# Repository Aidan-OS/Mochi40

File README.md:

# Mochi40
A 40% keyboard with an OLED and rotary encoder.

Files found on this GitHub should be fully functional. For more information come reach out [on my discord](https://discord.gg/kkPBkA3x4q)

# Ordering Guide
TODO

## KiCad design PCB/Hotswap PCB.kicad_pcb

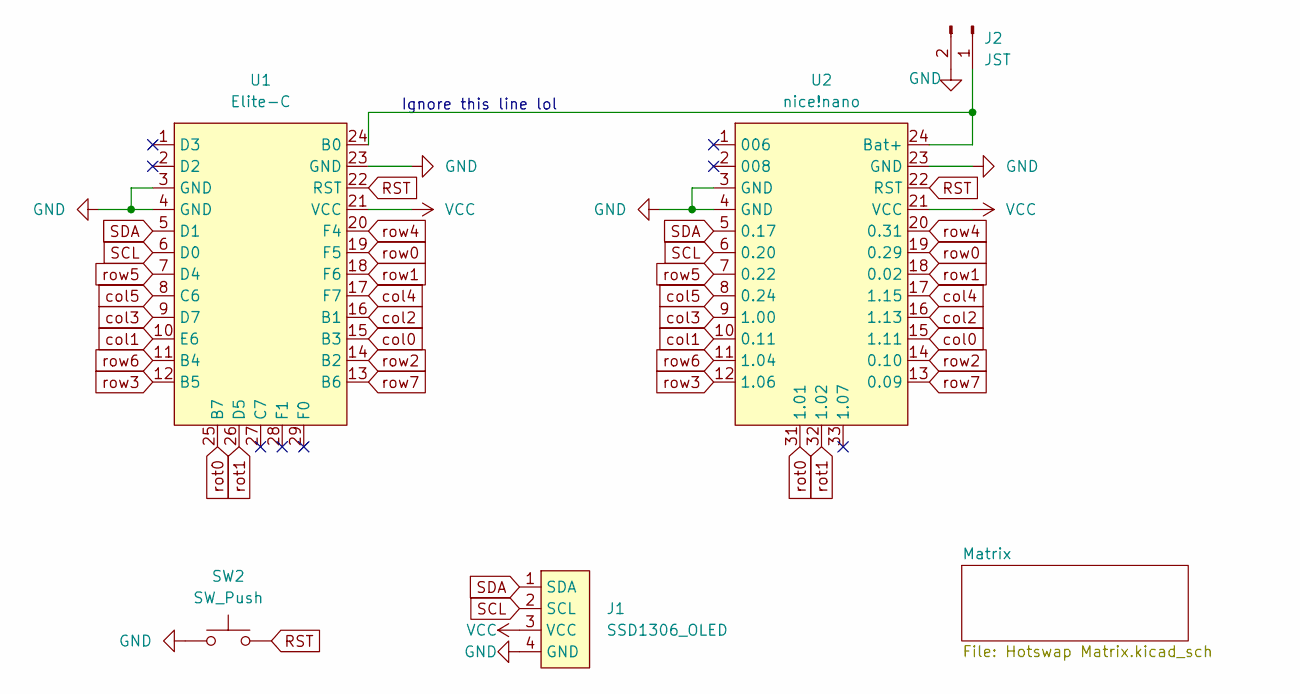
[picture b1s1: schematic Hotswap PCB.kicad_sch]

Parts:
J1: SSD1306_OLED; OLED_v2
J2: JST; JST_PH_S2B-PH-K_1x02_P2.00mm_Horizontal
SW2: SW_Push; SW_Tactile_SPST_Angled_MJTP1117
U1: Elite-C
U2: nice!nano; nice_nano

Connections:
GND: J1.4 (GND), J2.2, SW2.1, U1.3 (GND), U1.4 (GND), U1.23 (GND), U2.3 (GND), U2.4 (GND), U2.23 (GND); also elsewhere on the board
unnamed: J2.1, U1.24 (B0), U2.24 (Bat+)
RST: SW2.2, U1.22 (RST), U2.22 (RST)
SCL: J1.2 (SCL), U1.6 (D0), U2.6 (0.20)
SDA: J1.1 (SDA), U1.5 (D1), U2.5 (0.17)
VCC: J1.3 (VCC), U1.21 (VCC), U2.21 (VCC)
col0: U1.15 (B3), U2.15 (1.11); also elsewhere on the board
col1: U1.10 (E6), U2.10 (0.11); also elsewhere on the board
col2: U1.16 (B1), U2.16 (1.13); also elsewhere on the board
col3: U1.9 (D7), U2.9 (1.00); also elsewhere on the board
col4: U1.17 (F7), U2.17 (1.15); also elsewhere on the board
col5: U1.8 (C6), U2.8 (0.24); also elsewhere on the board
rot0: U1.25 (B7), U2.31 (1.01); also elsewhere on the board
rot1: U1.26 (D5), U2.32 (1.02); also elsewhere on the board
row0: U1.19 (F5), U2.19 (0.29); also elsewhere on the board
row1: U1.18 (F6), U2.18 (0.02); also elsewhere on the board
row2: U1.14 (B2), U2.14 (0.10); also elsewhere on the board
row3: U1.12 (B5), U2.12 (1.06); also elsewhere on the board
row4: U1.20 (F4), U2.20 (0.31); also elsewhere on the board
row5: U1.7 (D4), U2.7 (0.22); also elsewhere on the board
row6: U1.11 (B4), U2.11 (1.04); also elsewhere on the board
row7: U1.13 (B6), U2.13 (0.09); also elsewhere on the board

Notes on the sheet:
Ignore this line lol

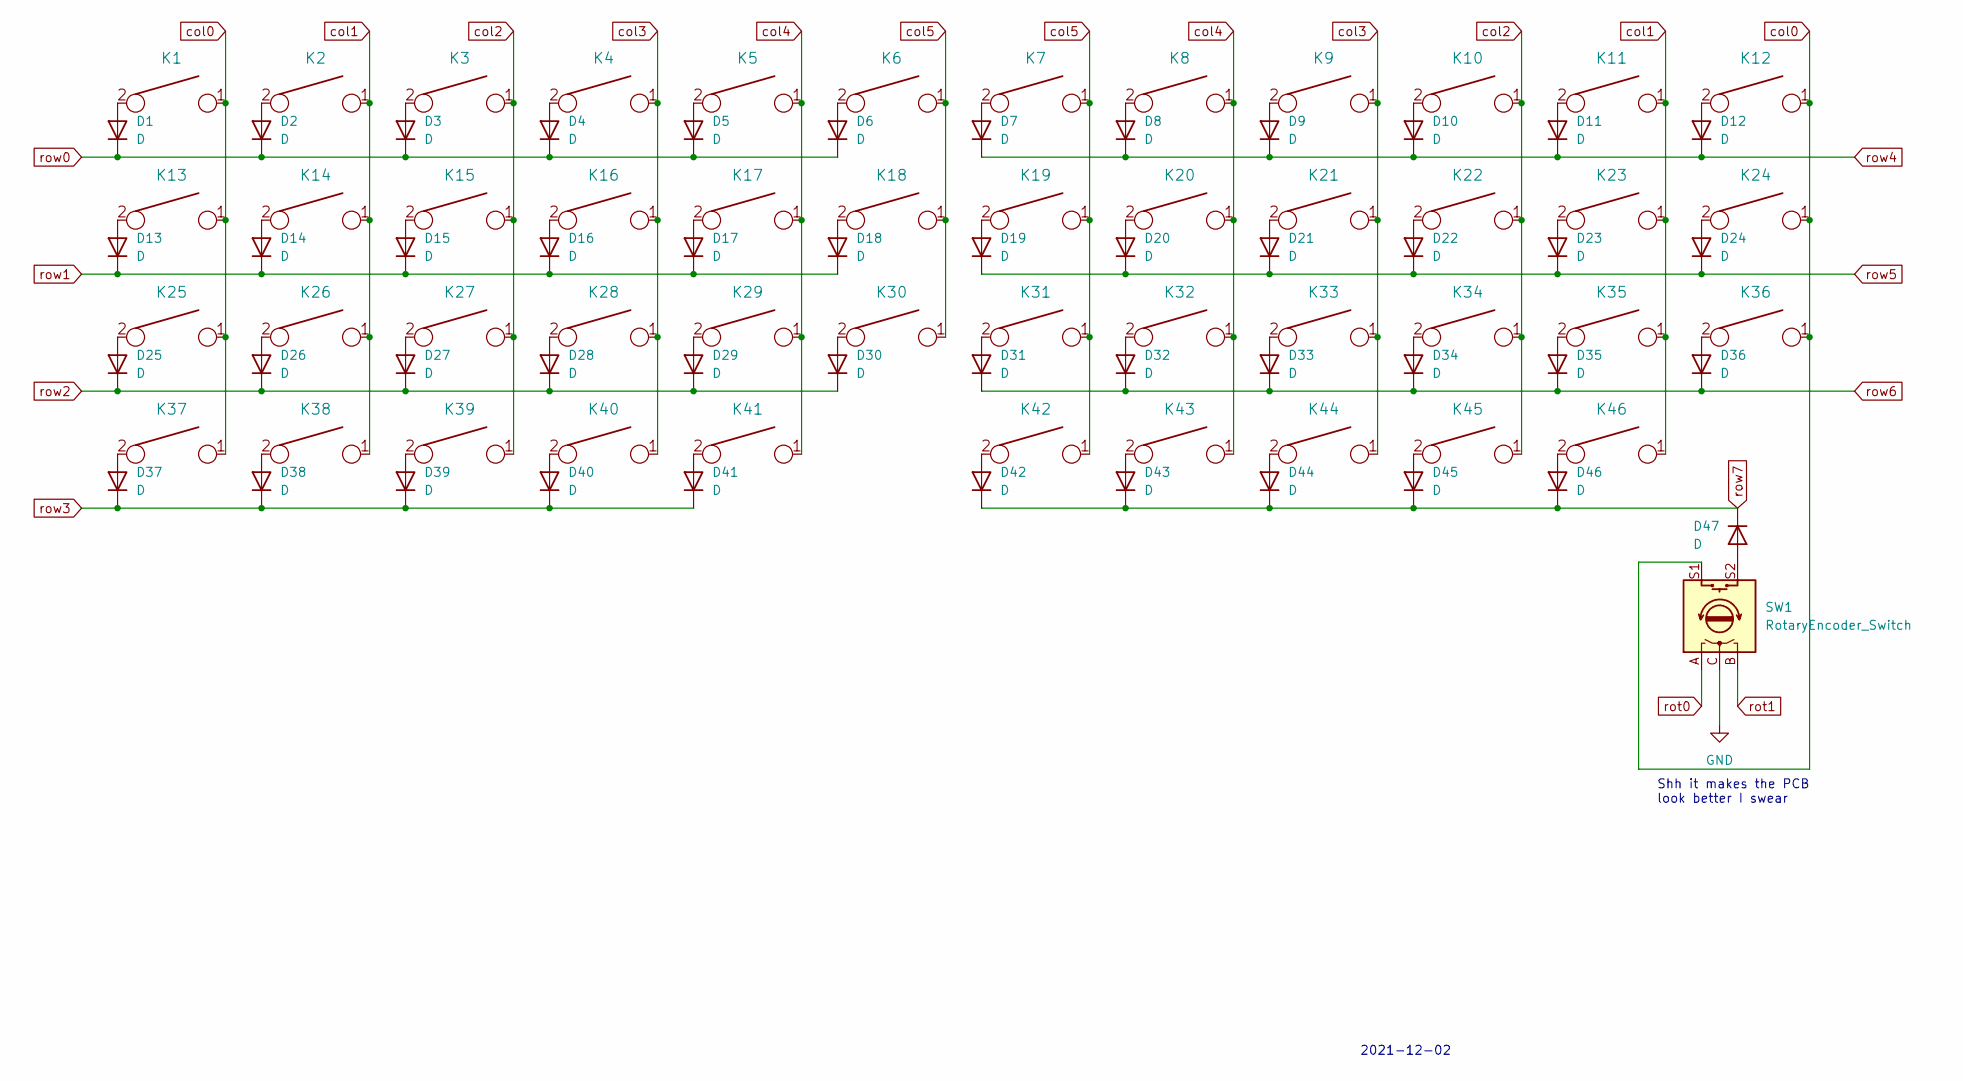
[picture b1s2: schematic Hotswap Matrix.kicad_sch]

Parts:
D1, D2, D3, D4, D5, D6, D7, D8, D9, D10, D11, D12, D13, D14, D15, D16, D17, D18, D19, D20, D21, D22, D23, D24, D25, D26, D27, D28, D29, D30, D31, D32, D33, D34, D35, D36, D37, D38, D39, D40, D41, D42, D43, D44, D45, D46, D47: D; Diode-Hybrid-Back
K1, K2, K3, K4, K5, K6, K7, K8, K9, K10, K11, K14, K15, K16, K17, K18, K19, K20, K21, K22, K23, K26, K27, K28, K29, K30, K31, K32, K33, K34, K35, K36, K37, K38, K39, K40, K43, K44, K45, K46: KEYSW; MXOnly-1U-NoLED
K12, K25: KEYSW; MXOnly-1.5U-NoLED
K13, K24, K41, K42: KEYSW; MXOnly-1.25U-NoLED
SW1: RotaryEncoder_Switch; RotaryEncoder_Alps_EC11E-Switch_Vertical_H20mm

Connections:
GND: SW1.C; also elsewhere on the board
unnamed: D1.2 (A), K1.2
unnamed: D2.2 (A), K2.2
unnamed: D3.2 (A), K3.2
unnamed: D4.2 (A), K4.2
unnamed: D5.2 (A), K5.2
unnamed: D6.2 (A), K6.2
unnamed: D7.2 (A), K7.2
unnamed: D8.2 (A), K8.2
unnamed: D9.2 (A), K9.2
unnamed: D10.2 (A), K10.2
unnamed: D11.2 (A), K11.2
unnamed: D12.2 (A), K12.2
unnamed: D13.2 (A), K13.2
unnamed: D14.2 (A), K14.2
unnamed: D15.2 (A), K15.2
unnamed: D16.2 (A), K16.2
unnamed: D17.2 (A), K17.2
unnamed: D18.2 (A), K18.2
unnamed: D19.2 (A), K19.2
unnamed: D20.2 (A), K20.2
unnamed: D21.2 (A), K21.2
unnamed: D22.2 (A), K22.2
unnamed: D23.2 (A), K23.2
unnamed: D24.2 (A), K24.2
unnamed: D25.2 (A), K25.2
unnamed: D26.2 (A), K26.2
unnamed: D27.2 (A), K27.2
unnamed: D28.2 (A), K28.2
unnamed: D29.2 (A), K29.2
unnamed: D30.2 (A), K30.2
unnamed: D31.2 (A), K31.2
unnamed: D32.2 (A), K32.2
unnamed: D33.2 (A), K33.2
unnamed: D34.2 (A), K34.2
unnamed: D35.2 (A), K35.2
unnamed: D36.2 (A), K36.2
unnamed: D37.2 (A), K37.2
unnamed: D38.2 (A), K38.2
unnamed: D39.2 (A), K39.2
unnamed: D40.2 (A), K40.2
unnamed: D41.2 (A), K41.2
unnamed: D42.2 (A), K42.2
unnamed: D43.2 (A), K43.2
unnamed: D44.2 (A), K44.2
unnamed: D45.2 (A), K45.2
unnamed: D46.2 (A), K46.2
unnamed: D47.2 (A), SW1.S2
col0: K1.1, K12.1, K13.1, K24.1, K25.1, K36.1, K37.1, SW1.S1; also elsewhere on the board
col1: K2.1, K11.1, K14.1, K23.1, K26.1, K35.1, K38.1, K46.1; also elsewhere on the board
col2: K3.1, K10.1, K15.1, K22.1, K27.1, K34.1, K39.1, K45.1; also elsewhere on the board
col3: K4.1, K9.1, K16.1, K21.1, K28.1, K33.1, K40.1, K44.1; also elsewhere on the board
col4: K5.1, K8.1, K17.1, K20.1, K29.1, K32.1, K41.1, K43.1; also elsewhere on the board
col5: K6.1, K7.1, K18.1, K19.1, K30.1, K31.1, K42.1; also elsewhere on the board
rot0: SW1.A; also elsewhere on the board
rot1: SW1.B; also elsewhere on the board
row0: D1.1 (K), D2.1 (K), D3.1 (K), D4.1 (K), D5.1 (K), D6.1 (K); also elsewhere on the board
row1: D13.1 (K), D14.1 (K), D15.1 (K), D16.1 (K), D17.1 (K), D18.1 (K); also elsewhere on the board
row2: D25.1 (K), D26.1 (K), D27.1 (K), D28.1 (K), D29.1 (K), D30.1 (K); also elsewhere on the board
row3: D37.1 (K), D38.1 (K), D39.1 (K), D40.1 (K), D41.1 (K); also elsewhere on the board
row4: D7.1 (K), D8.1 (K), D9.1 (K), D10.1 (K), D11.1 (K), D12.1 (K); also elsewhere on the board
row5: D19.1 (K), D20.1 (K), D21.1 (K), D22.1 (K), D23.1 (K), D24.1 (K); also elsewhere on the board
row6: D31.1 (K), D32.1 (K), D33.1 (K), D34.1 (K), D35.1 (K), D36.1 (K); also elsewhere on the board
row7: D42.1 (K), D43.1 (K), D44.1 (K), D45.1 (K), D46.1 (K), D47.1 (K); also elsewhere on the board

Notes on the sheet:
2021-12-02
Shh it makes the PCB look better I swear

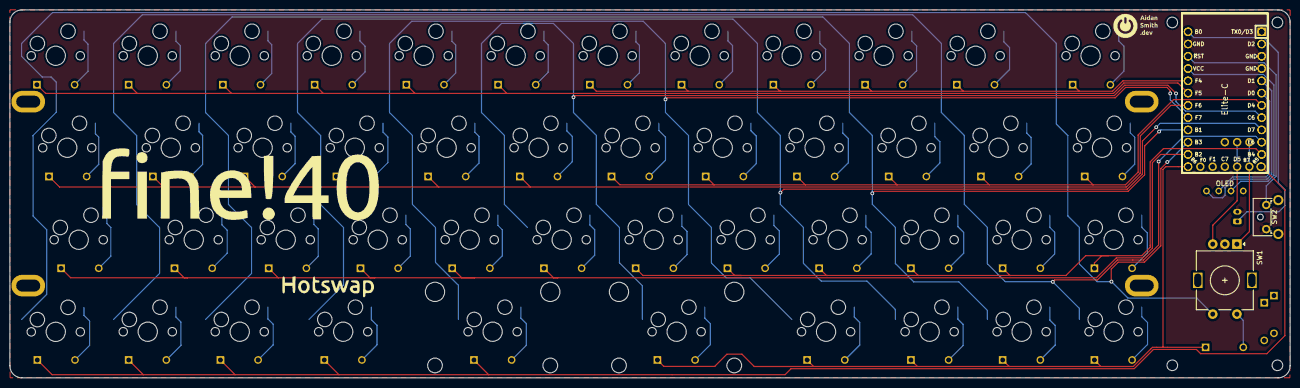
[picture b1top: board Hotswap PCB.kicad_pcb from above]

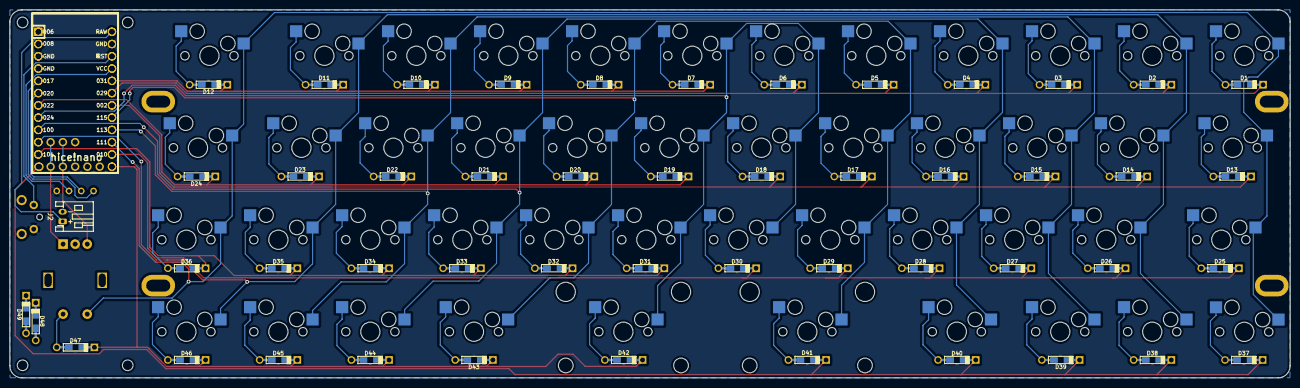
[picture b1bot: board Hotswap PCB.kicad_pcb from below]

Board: 2 copper layers, 265.1 x 76.2 mm, 109 parts (3 on the bottom side), 69 nets.

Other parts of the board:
Acryl Mount: MountingHole_2.2mm_M2
Acryl Mount#2, Acryl Mount#3, Acryl Mount#4: MountingHole_2.2mm_M2
D48, D49: D; Diode-Hybrid-Back
Mnt: PKRH
Mnt#2, Mnt#3, Mnt#4: PKRH

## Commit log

2021-12-07 Made a single mate to test discord integration
2021-12-10 Added QMK Firmware, added files needed for blender renders
2021-12-10 Added acrylic cover and the blender model for it
2021-12-11 Fixed plate.wrl and acrylic cover.wrl from being broken (why solidworks)
2021-12-13 Fixed a problem PCB Matrixes not being seperate. Uploaded somewhat broken ZMK firmware
2021-12-14 Fixed keymap, first pass at OLED (failed)
2021-12-14 Finished both firmwares
2021-12-15 prepared files for final send to PCBWay
2021-12-16 Confirming that everything is commited
2021-12-30 Added battery hole to CNC case. Fixed odd linkages with kicad files. General firmware updates
2022-01-08 Removed revision naming on PCB, fixed info.json so it will now properly work, added VIA compatiblility, Updated renders slightly
2022-01-08 Fixed some spacing issues with the via layout
2022-01-08 Made the fixes for QMK configurator actually work. Added ! to the places where it was missing
2022-01-08 3D print case now exists
2022-01-08 I didn't save before the last commit
2022-01-10 Beginning to draft IC
2022-01-25 Second revision for the IC
2022-02-22 Made changes to IC, slightly modified case file to deal with a tolerance issue present in the prototype
2022-02-22 Added submodules, fixed KiCad relative paths
2022-02-27 Slight changes to readme to direct people to the right place
2022-06-06 Added BOM
2022-06-06 BOM Didn't save for some reason
2022-06-06 Double screw up, missed i in a url
2022-06-19 Making sure all files are up to date
2022-06-22 Removed a couple markings
2023-04-24 Removing all solidworks files
